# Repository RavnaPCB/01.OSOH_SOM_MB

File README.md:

## ReadME

    STM32MP157 SOM [DBSTM32MP1]               - [Work In Progress]
    
    STM32MP157 Motherboard [MB10080_STM32MP1] - [Work In Progress]
    
## Introduction

I started this project a few months ago, in order to learn PCB Design, and deepen my electronics knowledge, with the intention to eventually publicly release the development files, so other people could learn from them and my mistakes, and maybe at some point, after all the issues are sorted out - use as a reference or put to actual use.

## Future Plans

> Develop a series of robust [OpenHardware] Systems On Module [SOM], Motherboards and Single Board Computers [SBC] capable of operating in the industrial temperature range, accompanied by detailed circuit explanations, spreadsheets, simulations and repair manuals.

## Software Requirements [OpenSource]

[KiCAD](https://www.kicad.org/) - A Cross Platform and Open Source Electronics Design Automation Suite

[LibreOFFICE](https://www.libreoffice.org)  - Office Suite

[FreeCAD](https://www.freecadweb.org/)  - 3D Parametric Modeler

[FEMM](https://www.femm.info/wiki/Download) - Finite Element Method Magnetics

[CommonLIB](https://github.com/IvanIlievOSOH/00.CommonLIB) - Custom KiCAD Library

## Knows Issues, Flaws and Quirks

> The components I picked are not the best ones currently in production, nor the most suitable ones, but when I started this project a few months ago, I had the intention to get the PCBs manufactured and assembled, so I had to work with what was available on Mouser and Digikey, but since a complete redesign will be necessary to fix some of the issues and the ongoing chip shortage is still going strong, the next revision will be a major one, using other, more suitable components, not necessarily available at the moment from the official distributors. The boards will be manufactured and assembled when the semiconductor crisis is over unless I a way to source the components

> There are some things that don't make much sense at first glance (unused pads, holes in the solder mask, unnecessary components and copper pours etc). Most are there intentionaly because I wanted to do some measurements and experiments with the PCBs in order to prove some rules and concepts to myself.

> There are also some very obvious and probably critical "SI" and "PI" issues (Dual Stripline traces running parallel to eachother longer than they should, one of the eMMC Flash power rails routed as a relatively narrow trace on an outside layer etc.). I will be reporting and describing every issue I find in the repository's "Issues" tab.

> In hindsight, most of the issues and mistakes could have easily been avoided at an earlier stage of the design, if more research was done, but I decided to upload everything now, as a [Work In Progress], so I can hopefully get some constructive criticism and suggestoins before I start redesigning the boards.

    All your feedback, cirticism, help and suggestions will be greatly appreciated.

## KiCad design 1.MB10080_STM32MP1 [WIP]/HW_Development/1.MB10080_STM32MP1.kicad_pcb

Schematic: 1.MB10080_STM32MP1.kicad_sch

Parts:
C1, C2, C3, C4, C5, C6, C7, C8, C9, C10, C11, C13, C15, C16, C18, C19, C20, C21, C22, C23, C26, C27, C28, C29, C30, C33, C34, C37, C38, C39, C44, C45, C47, C48, C49, C53, C54, C55, C56, C57, C58, C59, C60, C61, C62, C63, C64, C65, C70, C71, C72, C73, C74, C78, C79, C80, C84, C85, C86, C87, C90, C91, C92, C93, C94, C95, C98, C99, C100, C101, C106, C113, C114, C115, C116, C117, C118, C119, C131, C132, C133, C137, C138, C139, C140, C141: 0.1uF; C_0402
C12, C31, C35, C88: 47uF; C_0805
C14: 220uF; CP_10x10
C17, C24, C25, C46, C50, C51, C52, C68, C69, C76, C77, C83, C96, C97, C104, C105, C111, C112, C134, C135: 0.1uF; C_0805
C32, C36, C89: 10uF; C_0402
C40, C41, C42, C43, C66, C67, C81, C82: C; C_0402
C75: 0.1uF; CP_2312
C102, C103: 1uF; C_0805
C122, C123, C124: 100uF; CP_2312
D2: D; D_0805
D6, D8: D
H1, H2, H3, H4, H5, H6, H7: MountingHole_Pad; MountingHole-[2.2]-PAD-M2
J1, J7: Connector_1x4; CUI_TB006-508-04BE
J2: Connector_1x6; CUI_TB006-508-06BE
J3: Connector_1x6; CUI_MD-30SM
J5: USB_A_Stacked; AU-Y1008-2
J6, J8: FX10A-120S-P-SV
J9: 8P8C_0955016890; 0955016890
L1, L9: 4.7uH; XGL-4040
L2, L3, L4, L5, L6, L7: L; L_0805
L100: 4.7uH; XAL-8080
Q1, Q2: SiSS76LDN; PowerPAK-1212-8S
Q5, Q6: CSD17327Q5A; SON-[5x6]
R1, R2, R3, R4, R5, R6, R7, R8, R11, R12, R14, R15, R17, R18, R27, R28, R29, R30, R33, R34, R39, R40: R; R_0402
R9: 0R; R_2512
R10, R13, R16, R19, R20, R21, R22, R23, R32, R38: 0R; R_0402
R24, R25, R26, R31: 0.007; R_0402
TP1, TP2, TP6, TP7, TP9, TP10: TP; TP-[R0402-PAD]
U1: LM3150; HTSSOP-14-[4.4x5]-[P0.65]
U2: LTC4368; MSOP-10-[3x3]-[P0.5]
U3, U13: RT6206; WDFN-10L-[3x3]-[P0.5]
U4: DS90UR905QSQ/NOPB; WQFN-48-[P0.5]
U5: LM3526; SOIC-08-[13.9x4.9]-[P1.27]
U6, U7: TUSB213; VQFN-14
U8: DP83TD510ERHBR; QFN-32-[5x5]-[P0.5]
U9: LP38798; WSON-12-[4x4]-[P0.5]
U11: DS15BA101; WSON-08-[3x3]-[P0.5]
U12: TJA1042; HVSON-8-[3x3]-[P0.65]
Y1: 2P_OSC

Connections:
1V8: C50.2, C51.2, C52.2, C53.2, C54.2, C55.2, C63.2, C64.2, C65.2, C68.2, C69.2, C70.2, C71.2, C72.2, C73.2, L5.1, L6.1, L7.1, R24.1, U4.24 (VODSEL), U9.10 (OUT_FB), U9.11 (OUT), U9.12 (OUT)
3V3: C18.2, C23.2, C24.2, C25.2, C26.2, C27.2, C28.2, C29.2, C30.2, C46.2, C75.2, C76.2, C77.2, C78.2, C79.2, C80.2, C83.2, C84.2, C85.2, C87.2, C90.2, C92.2, C93.2, C94.2, C95.2, C96.2, C97.2, L1.2, L2.1, L3.1, L4.1, R17.1, R19.2, R29.1, R30.1, R31.2, U9.1 (VIN), U9.2 (VIN), U9.3 (VIN_CP), U11.5 (VCC)
5V: C12.2, C36.2, C88.2, C89.2, C133.2, C134.2, C135.2, C137.2, C138.2, C139.2, C140.2, C141.2, L9.2, R11.1, R14.1, R39.1, U6.12 (VCC), U7.12 (VCC)
/DCMI_D00: J6.49
/DCMI_D01[TIM5_CH1]: J6.36
/DCMI_D02: J6.53
/DCMI_D03: J6.47
/DCMI_D04[TIM8_CH2N]: J6.55
/DCMI_D05: J6.68
/DCMI_D06[TIM8_CH2]: J6.58
/DCMI_D07: J6.56
/DCMI_D08: J6.41
/DCMI_D09[TIM8_CH4]: J6.50
/DCMI_D10[TIM8_ETR]: J6.46
/DCMI_D11: J6.34
/DCMI_D12: J6.64
/DCMI_D13[TIM5_CH4]: J6.44
/DCMI_HSYNC[TIM5_ETR]: J6.43
/DCMI_PXCLK: J6.62
/DCMI_VSYNC[TIM8_CH1]: J6.52
/DSI_CKN: J6.15
/DSI_CKP: J6.11
/DSI_D0N: J6.23
/DSI_D0P: J6.19
/DSI_D1N: J6.7
/DSI_D1P: J6.3
/EN: C1.2, U1.3 (EN)
/ETH_CLK: J8.90
/ETH_COL: J8.86
/ETH_CRS: J8.82
/ETH_GTXCLK: J8.78
/ETH_MDC: J8.70
/ETH_MDIO: J8.66
/ETH_RXCLK: J8.98
/ETH_RXD00: J8.89
/ETH_RXD01: J8.93
/ETH_RXD02: J8.97
/ETH_RXD03: J8.101
/ETH_RXDV: J8.94
/ETH_RXER: J8.102
/ETH_TXCLK: J8.69
/ETH_TXD00: J8.85
/ETH_TXD01: J8.81
/ETH_TXD02: J8.77
/ETH_TXD03: J8.73
/ETH_TXEN: J8.65
/ETH_TXER: J8.74
/FAULT: U2.7 (FAULT)
/FB: C5.1, C7.1, R4.2, R5.2, U1.4 (FB)
/FDCAN1_RX: J8.34
/FDCAN1_TX: J8.36
/GATE: U2.10 (GATE)
/GPIO[TIM8_CH3N]: J6.40
/HDMI-CEC: J6.59
/I2C1_SCL: J8.62
/I2C1_SDA: J8.58
/I2C2_SCL: J6.37
/I2C2_SDA: J6.35
/I2C4_SCL: J6.10
/I2C4_SDA: J6.12
/I2S1_CK: J6.31
/I2S1_MCK: J6.22
/I2S1_SDI: J6.28
/I2S1_SDO: J6.24
/I2S1_WS: J6.30
/LTDC-B00: J6.82, U4.43 (B0)
/LTDC-B01: J6.80, U4.44 (B1)
/LTDC-B02: J6.79, U4.45 (B2)
/LTDC-B03: J6.61, U4.46 (B3)
/LTDC-B04: J6.76, U4.47 (B4)
/LTDC-B05: J6.74, U4.48 (B5)
/LTDC-B06: J6.73, U4.1 (B6)
/LTDC-B07: J6.71, U4.2 (B7)
/LTDC-CLK: J6.83, U4.10 (PCLK)
/LTDC-DE: J6.67, U4.5 (DE)
/LTDC-G00: J6.94, U4.35 (G0)
/LTDC-G01: J6.92, U4.36 (G1)
/LTDC-G02[TIM8_CH1N]: J6.86, U4.37 (G2)
/LTDC-G03: J6.89, U4.38 (G3)
/LTDC-G04: J6.88, U4.39 (G4)
/LTDC-G05[TIM8_CH3]: J6.65, U4.40 (G5)
/LTDC-G06[TIM8_BKIN2]: J6.85, U4.41 (G6)
/LTDC-G07[TIM8_BKIN1]: J6.70, U4.42 (G7)
/LTDC-HSYNC: J6.95, U4.3 (HS)
/LTDC-R00: J6.106, U4.25 (R0)
/LTDC-R01: J6.104, U4.26 (R1)
/LTDC-R02: J6.103, U4.27 (R2)
/LTDC-R03: J6.101, U4.28 (R3)
/LTDC-R04: J6.100, U4.29 (R4)
/LTDC-R05[TIM5_CH2]: J6.77, U4.32 (R5)
/LTDC-R06[TIM5_CH3]: J6.97, U4.33 (R6)
/LTDC-R07: J6.98, U4.34 (R7)
/LTDC-VSYNC: J6.91, U4.4 (VS)
/NRST: J8.31
/OV: C15.2, R7.2, R8.1, TP2.1, U2.3 (OV)
/RETRY: C16.2, U2.4 (RETRY)
/RX+: R21.1, U8.5 (RX+)
/RX-: R23.1, U8.6 (RX-)
/SENSE: R9.1, U2.9 (SENSE)
/SHDN: U2.6 (SHDN)
/SPI4_MISO: J6.4
/SPI4_MOSI: J6.6
/SPI4_NSS: J6.18
/SPI4_SCK: J6.16
/SW: C3.1, C21.2, C131.2, L1.1, L9.1, L100.1, R2.1, R3.1, TP7.1, TP10.1, U1.10 (SW), U3.6 (SW), U3.7 (SW), U13.6 (SW), U13.7 (SW)
/TX+: R20.1, U8.4 (TX+)
/TX-: R22.1, U8.7 (TX-)
/USART3_CTS: J8.41
/USART3_RTS: J8.43
/USART3_RX: J8.47
/USART3_TX: J8.49
/USB_D1+: J8.46
/USB_D1-: J8.42
/USB_D2+: J8.50
/USB_D2-: J8.54
/USB_OTG_ID: J8.37
/USB_VBUS: J8.35
/UV: C13.2, R6.2, R7.1, TP1.1, U2.2 (UV)
/VBAT_IN: J8.59, J8.61
/VCC_DCDC: C4.2, D2.2 (A), U1.1 (VCC)
/VDDA: C31.2, C32.2, C33.2, C34.2, L2.2, U8.3 (VDDA_3V3)
/VDDIO: C35.2, C37.2, C38.2, C48.2, C49.2, L3.2, L4.2, U4.30 (VDDIO), U8.17 (VDDIO)
/VDDL: C57.2, C60.2, L6.2, U4.7 (VDDL)
/VDDP: C58.2, C61.2, L7.2, U4.14 (VDDP)
/VDDTXHS: C56.2, C59.2, L5.2, U4.17 (VDDHS), U4.22 (VDDTX)
/WKUP3-TAMPOUT2: J8.53
/WKUP4-TAMPIN2: J8.55
DCDCOUT: C6.2, C7.2, C17.2, C20.2, C74.2, C86.2, C99.2, C101.2, C106.2, C111.2, C112.2, C113.2, C114.2, C115.2, C116.2, C117.2, C119.2, C122.1, C123.1, C124.1, D6.2 (A), D8.2 (A), J6.111, J6.112, J6.113, J6.114, J6.115, J6.116, J6.117, J6.118, J6.119, J6.120, J8.1, J8.2, J8.3, J8.4, J8.5, J8.6, J8.7, J8.8, J8.9, J8.10, J8.12, J8.14, J8.16, J8.18, J8.20, J8.22, J8.111, J8.112, J8.113, J8.114, J8.115, J8.116, J8.117, J8.118, J8.119, J8.120, L100.2, R4.1, U3.9 (VIN), U3.10 (VIN), U13.9 (VIN), U13.10 (VIN)
GND: C1.1, C2.1, C4.1, C8.1, C9.1, C10.1, C11.1, C12.1, C13.1, C14.2, C15.1, C16.1, C17.1, C18.1, C19.1, C20.1, C22.1, C24.1, C25.1, C26.1, C27.1, C28.1, C29.1, C30.1, C31.1, C32.1, C33.1, C34.1, C35.1, C36.1, C37.1, C38.1, C39.1, C40.2, C41.2, C44.1, C45.1, C46.1, C47.1, C48.1, C49.1, C50.1, C51.1, C52.1, C53.1, C54.1, C55.1, C56.1, C57.1, C58.1, C59.1, C60.1, C61.1, C62.1, C63.1, C64.1, C65.1, C68.1, C69.1, C70.1, C71.1, C72.1, C73.1, C74.1, C75.1, C76.1, C77.1, C78.1, C79.1, C80.1, C83.1, C84.1, C85.1, C86.1, C87.1, C88.1, C89.1, C90.1, C91.1, C92.1, C93.1, C94.1, C95.1, C96.1, C97.1, C98.1, C99.1, C100.1, C101.1, C102.1, C103.1, C104.1, C105.1, C106.1, C111.1, C112.1, C113.1, C114.1, C115.1, C116.1, C117.1, C118.1, C119.1, C122.2, C123.2, C124.2, C132.1, C134.1, C135.1, C137.1, C138.1, C139.1, C140.1, C141.1, J1.3, J1.4, J6.1, J6.2, J6.5, J6.8, J6.9, J6.13, J6.14, J6.17, J6.20, J6.21, J6.25, J6.26, J6.27, J6.29, J6.32, J6.33, J6.38, J6.39, J6.42, J6.45, J6.48, J6.51, J6.54, J6.57, J6.60, J6.63, J6.66, J6.69, J6.72, J6.75, J6.78, J6.81, J6.84, J6.87, J6.90, J6.93, J6.96, J6.99, J6.102, J6.105, J6.107, J6.108, J6.109, J6.110, J8.11, J8.13, J8.15, J8.17, J8.19, J8.21, J8.23, J8.24, J8.25, J8.26, J8.27, J8.28, J8.29, J8.30, J8.32, J8.33, J8.38, J8.39, J8.40, J8.44, J8.45, J8.48, J8.51, J8.52, J8.56, J8.57, J8.60, J8.63, J8.64, J8.67, J8.68, J8.71, J8.72, J8.75, J8.76, J8.79, J8.80, J8.83, J8.84, J8.87, J8.88, J8.91, J8.92, J8.95, J8.96, J8.99, J8.100, J8.103, J8.104, J8.105, J8.106, J8.107, J8.108, J8.109, J8.110, R5.1, R8.2, R10.1, R12.2, R13.1, R15.2, R18.2, R25.1, R26.1, R34.2, R40.2, U1.5 (SGND), U1.9 (SGND), U1.14 (PGND), U1.EP, U2.5 (GND), U4.11 (RFB), U4.12 (CONFIG0), U4.13 (CONFIG1), U4.15 (RES0), U4.16 (RES1), U4.18 (RES2), U4.49 (EPAD), U6.7 (GND), U7.7 (GND), U8.33 (PAD), U9.6 (GND_CP), U9.7 (GND), U9.13 (GND), U11.3 (GND), U11.6 (GND)
unnamed: C2.2, U1.6 (SS)
unnamed: C3.2, D2.1 (K), U1.12 (BST)
unnamed: C5.2, C6.1, R3.2
unnamed: C19.2, R16.1, U3.3 (VREG5)
unnamed: C21.1, D6.1 (K), U3.8 (BOOT)
unnamed: C22.2, U3.4 (SS)
unnamed: C23.1, R17.2, R18.1, U3.2 (FB)
unnamed: C39.2, U8.1 (DVDD), U8.2 (CEXT)
unnamed: C40.1, U8.9 (XO), Y1.2
unnamed: C41.1, U8.10 (XI), Y1.1
unnamed: C42.1, R20.2, R21.2
unnamed: C42.2, C44.2
unnamed: C43.1, R22.2, R23.2
unnamed: C43.2, C45.2
unnamed: C47.2, U6.14 (RSTN)
unnamed: C62.2, U6.8 (VREG)
unnamed: C66.1, R28.1, U11.1 (INP)
unnamed: C66.2, R27.1, U4.20 (DOUT+)
unnamed: C67.1, R28.2, U11.2 (INN)
unnamed: C67.2, R27.2, U4.19 (DOUT-)
unnamed: C81.2, R30.2, U11.8 (OUTP)
unnamed: C82.2, R29.2, U11.7 (OUTN)
unnamed: C91.2, U9.4 (CP)
unnamed: C98.2, U7.14 (RSTN)
unnamed: C100.2, U7.8 (VREG)
unnamed: C118.2, R38.1, U13.3 (VREG5)
unnamed: C131.1, D8.1 (K), U13.8 (BOOT)
unnamed: C132.2, U13.4 (SS)
unnamed: C133.1, R39.2, R40.1, U13.2 (FB)
unnamed: Q1.1 (S), Q1.2 (S), Q1.3 (S)
unnamed: Q1.5 (D), Q1.6 (S), Q1.7 (S), Q1.8 (S)
unnamed: Q2.1 (S), Q2.2 (S), Q2.3 (S)
unnamed: Q2.5 (D), Q2.6 (S), Q2.7 (S), Q2.8 (S)
unnamed: Q5.1 (S), Q5.2 (S), Q5.3 (S)
unnamed: Q5.5 (D), Q5.6 (S), Q5.7 (S), Q5.8 (S)
unnamed: Q6.1 (S), Q6.2 (S), Q6.3 (S)
unnamed: Q6.5 (D), Q6.6 (S), Q6.7 (S), Q6.8 (S)
unnamed: R1.2, U1.7 (RON)
unnamed: R2.2, U1.8 (ILIM)
unnamed: R10.2, U6.1 (EQ)
unnamed: R11.2, R12.1, U6.4 (DC_BOOST/ENA_HS)
unnamed: R13.2, U7.1 (EQ)
unnamed: R14.2, R15.1, U7.4 (DC_BOOST/ENA_HS)
unnamed: R16.2, TP6.1, U3.5 (PGOOD)
unnamed: R19.1, U8.21 (PWDN_INT)
unnamed: R24.2, R25.2, U4.6 (IDX)
unnamed: R26.2, U4.23 (DE-EMPH)
unnamed: R31.1, U11.4 (Rvo)
unnamed: R32.2, U9.5 (EN)
unnamed: R33.1, U9.9 (SET)
unnamed: R33.2, R34.1, U9.8 (FB)
unnamed: R38.2, TP9.1, U13.5 (PGOOD)
VIN: C10.2, C11.2, J1.1, J1.2, R6.1, U2.1 (VIN)
VOUT: C8.2, C9.2, C14.1, C102.2, C103.2, C104.2, C105.2, R1.1, R9.2, U1.2 (VIN), U2.8 (VOUT)

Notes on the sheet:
PLACE ON TOP LAYER - FOR TESTING ONLY
100V UV/OV And Reverse Voltage Protection Controller With Bidirectional Circuit Breaker
LTC4368
Operating Voltage Range: 2.5V - 60V +/- 1.5% Overvoltage Protection: 100V Reverse Supply Protection: -40V

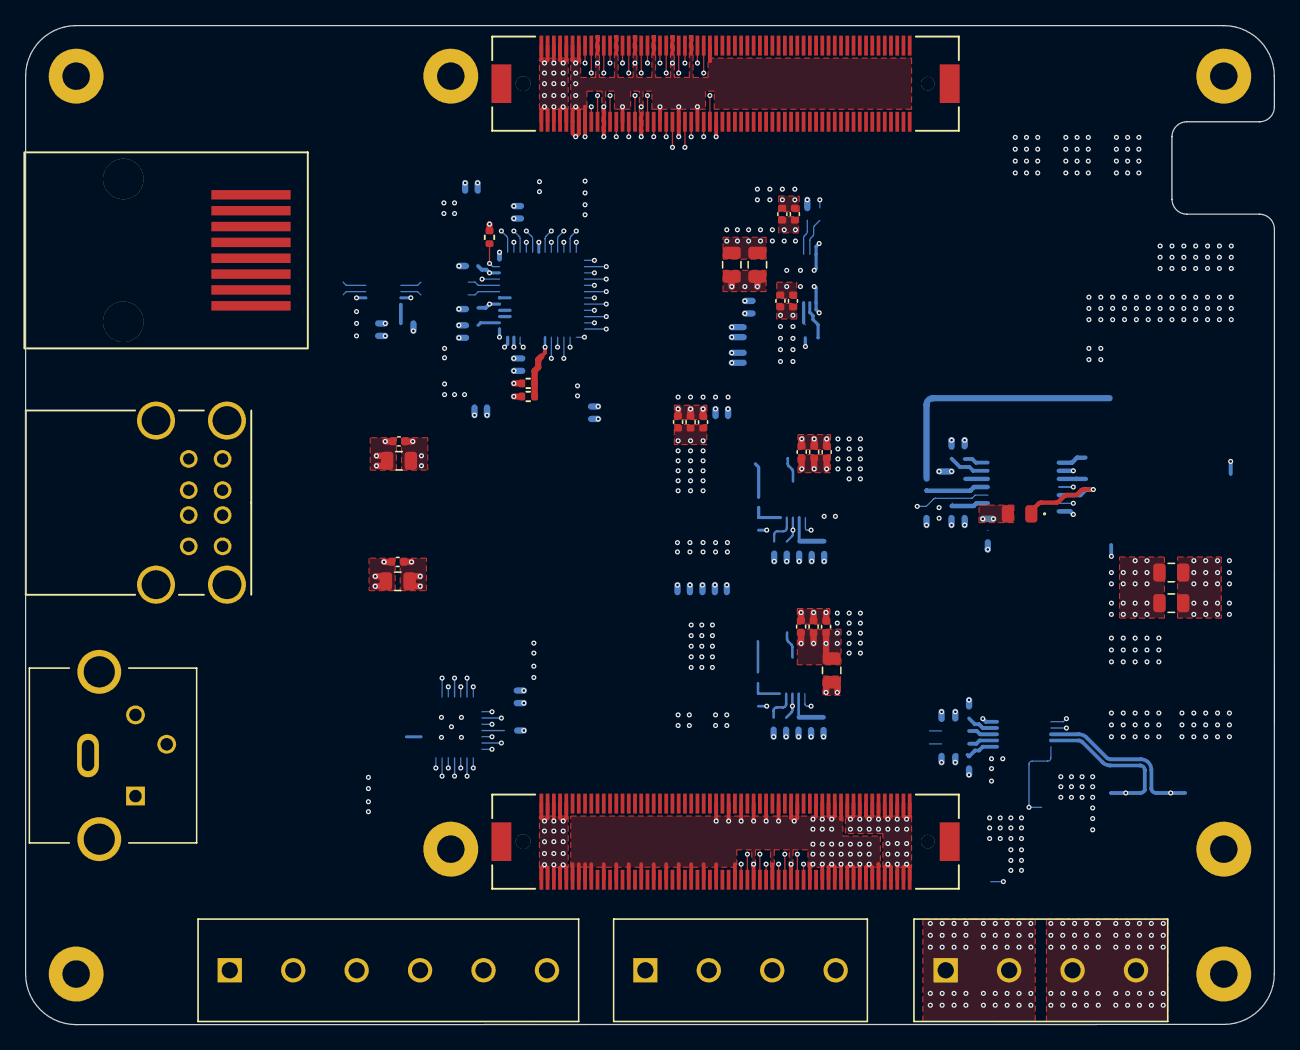
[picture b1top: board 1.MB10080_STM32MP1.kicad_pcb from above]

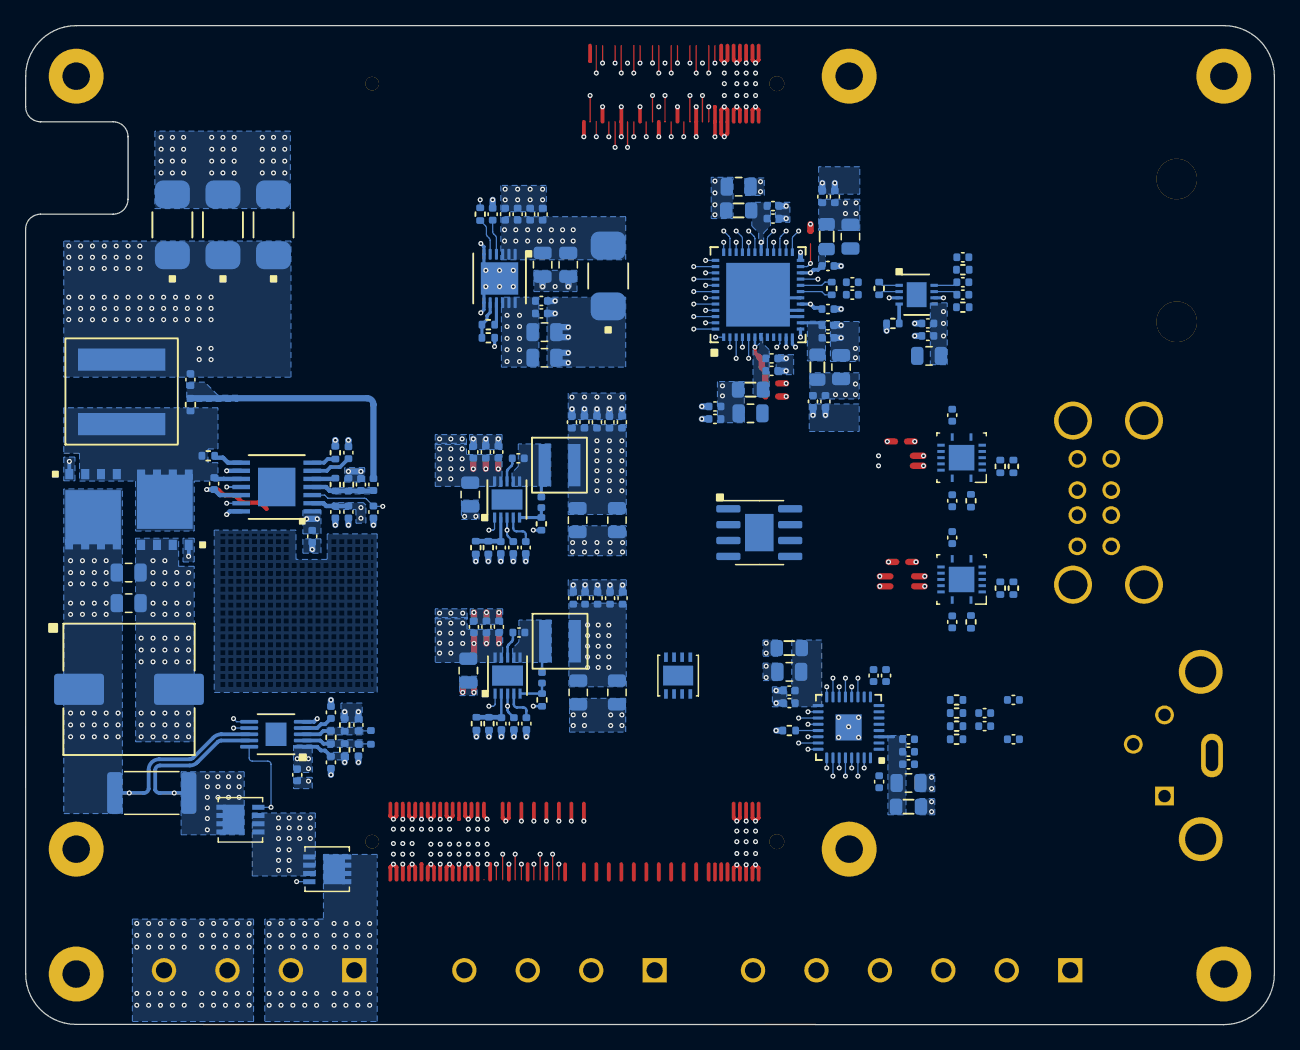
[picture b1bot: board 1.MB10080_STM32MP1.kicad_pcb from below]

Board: 6 copper layers, 100.0 x 80.0 mm, 212 parts (171 on the bottom side), 105 nets.

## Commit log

2022-04-25 Minor Board Changes
2022-04-25 Library Changes
2022-07-10 Delete 1.DBSTM32MP1 [WIP]/Datasheets directory
    Deleted because of a potential license conflict
